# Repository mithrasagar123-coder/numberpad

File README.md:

# Numberpad

## Overview 

Behold! It is a numerical keypad that one may utilize to transcribe numerals. This splendiferous device will ensure that you can type as many numbers as your heart desires.

I designed this for my Week 5 project of halflife, a 10-week program where you can design and build hardware projects free of cost!

## Parts
* XIAO-nRF52840-SMD as the main microcontroller
* Four test points 
* 14 standard buttons and 3 big buttons to tap tap tap
* Diodes to prevent ghosting

## Schematic

## Board

## BOM
| Item | Qty | Supplier | Cost/item | Total Cost | Link |
|:---|:---|:---|:---|:---|:---|
| Seeed Studio XIAO nRF52840 | 1 | Seeed Studio | $4.99 | $4.99 | https://www.seeedstudio.com/Seeed-XIAO-BLE-nRF52840-p-5201.html?srsltid=AYCX9vLsY7zQQ4J1BxVNNOp9EBk7qKUEgk98Upe8GNEmZq4AKlAtIVR- |
| Keyboard hotswaps | 1 | Seeed Studio | $4.99 | $4.99 | ht
| Keyboard diodes 100pc | 1 | Amazon | $5.99 | $5.99 | https://www.amazon.com/Values-Switching-Recovery-Schottky-Rectifier/dp/B0D69Q6HXG/ref=sr_1_5?crid=ZRDEF7B4UF2C&dib=eyJ2IjoiMSJ9.zTXQrWobcfrHy7zOETXIjDRbmhPvQHa7WzTS4K5c7TtKBZmLvVPBBDGVQXcNNWnK3vHg6yybH8pVVuPdHUkF9WpLBnhPQ-BHFcxt8NnhxZ0JTi1DlANXWLTHb9LwpntcUGzXqZSMfTip11WtaIwqxSshLRQHVyd31PiwUklmBeasQo6x6BTMSYSnXaHhRht2aURJwXJJocz58Id0048wDufCg6wU0xVlsLu6lf77jNc.h6aZ6KuAbeSEJpQf2htEpvuIdWCliIb4IAxqaitKhro&dib_tag=se&keywords=1N5819%2Bdiodes&qid=1794433047&sprefix=1n5819%2Bdiode%2Caps%2C191&sr=8-5&th=1 |
| PCB | 1 | JLCPCB | $4.90 | $4.90 | https://cart.jlcpcb.com/quote?stencilLayer=2&stencilWidth=100&stencilLength=100&stencilCounts=5&plateType=1&spm=Jlcpcb.Homepage.1010&spm=Jlcpcb.Instantquote&_t=1794432060372&up_spm=Jlcpcb.Loginpage.1003 |
| Estimated total shipping |  |  |  | $8.23 |  |
| **Total** |  |  |  | **$** |  |

Thanks for reading!

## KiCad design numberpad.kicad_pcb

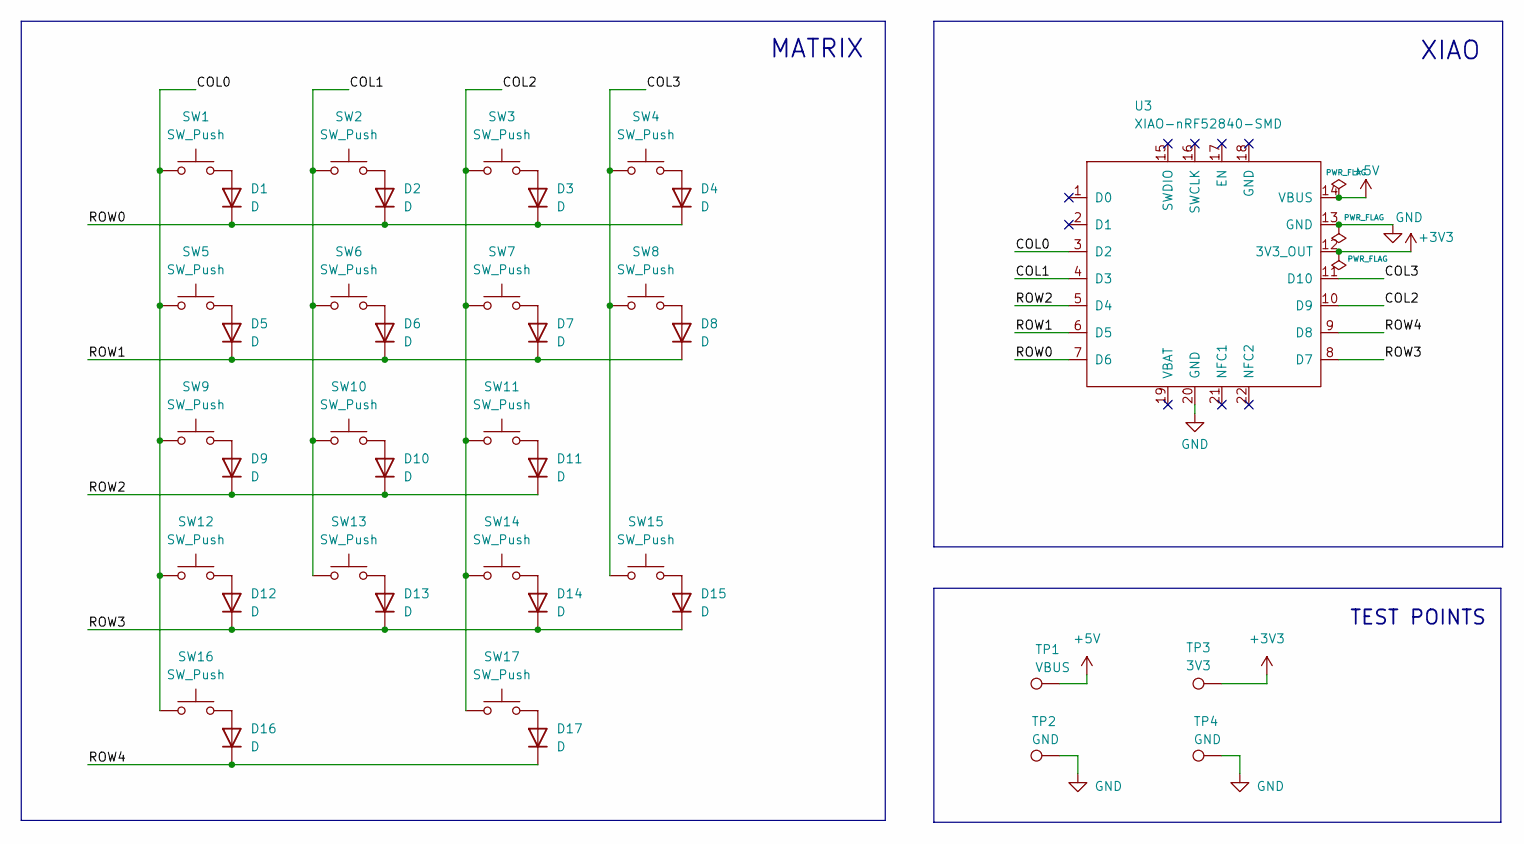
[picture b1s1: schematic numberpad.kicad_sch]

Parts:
D1, D2, D3, D4, D5, D6, D7, D8, D9, D10, D11, D12, D13, D14, D15, D16, D17: D; D_SOD-123
SW1, SW2, SW3, SW4, SW5, SW6, SW7, SW8, SW9, SW10, SW11, SW12, SW13, SW14, SW15, SW16, SW17: SW_Push; SW_choc_v2_HS_CPG135001S30_1u
TP1: VBUS; TestPoint_Pad_D2.0mm
TP2, TP4: GND; TestPoint_Pad_D2.0mm
TP3: 3V3; TestPoint_Pad_D2.0mm
U3: XIAO-nRF52840-SMD; modified-XIAO-nRF52840-SMD

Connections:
+3V3: TP3.1 (1_1), U3.12 (3V3_OUT)
+5V: TP1.1 (1_1), U3.14 (VBUS)
/COL0: SW1.1, SW5.1, SW9.1, SW12.1, SW16.1, U3.3 (D2)
/COL1: SW2.1, SW6.1, SW10.1, SW13.1, U3.4 (D3)
/COL2: SW3.1, SW7.1, SW11.1, SW14.1, SW17.1, U3.10 (D9)
/COL3: SW4.1, SW8.1, SW15.1, U3.11 (D10)
/ROW0: D1.1 (K), D2.1 (K), D3.1 (K), D4.1 (K), U3.7 (D6)
/ROW1: D5.1 (K), D6.1 (K), D7.1 (K), D8.1 (K), U3.6 (D5)
/ROW2: D9.1 (K), D10.1 (K), D11.1 (K), U3.5 (D4)
/ROW3: D12.1 (K), D13.1 (K), D14.1 (K), D15.1 (K), U3.8 (D7)
/ROW4: D16.1 (K), D17.1 (K), U3.9 (D8)
GND: TP2.1 (1_1), TP4.1 (1_1), U3.13 (GND), U3.20 (GND)
unnamed: D1.2 (A), SW1.2
unnamed: D2.2 (A), SW2.2
unnamed: D3.2 (A), SW3.2
unnamed: D4.2 (A), SW4.2
unnamed: D5.2 (A), SW5.2
unnamed: D6.2 (A), SW6.2
unnamed: D7.2 (A), SW7.2
unnamed: D8.2 (A), SW8.2
unnamed: D9.2 (A), SW9.2
unnamed: D10.2 (A), SW10.2
unnamed: D11.2 (A), SW11.2
unnamed: D12.2 (A), SW12.2
unnamed: D13.2 (A), SW13.2
unnamed: D14.2 (A), SW14.2
unnamed: D15.2 (A), SW15.2
unnamed: D16.2 (A), SW16.2
unnamed: D17.2 (A), SW17.2

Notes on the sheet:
TEST POINTS
MATRIX
XIAO

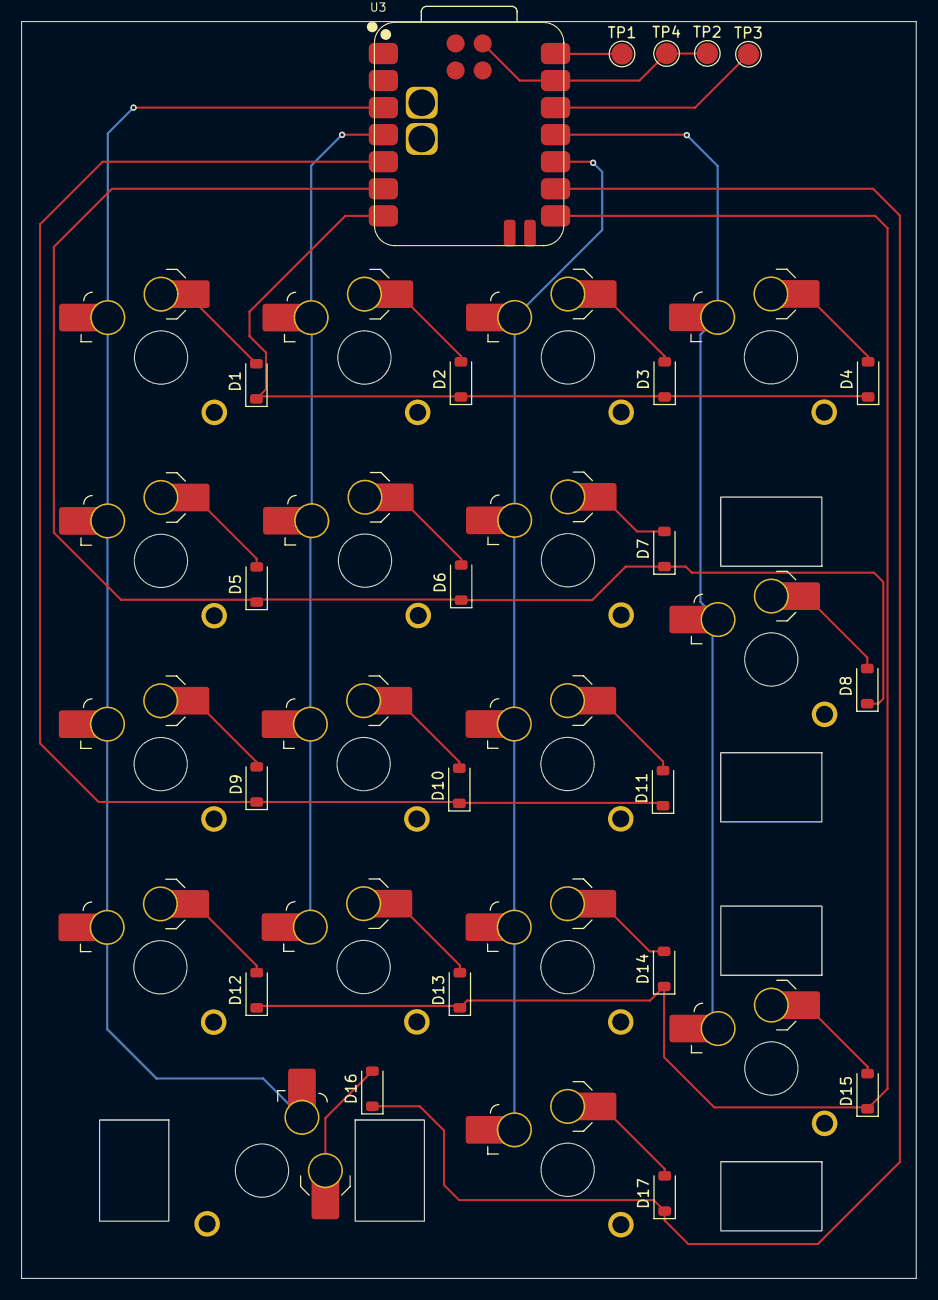
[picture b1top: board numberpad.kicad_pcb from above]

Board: 2 copper layers, 84.0 x 118.0 mm, 39 parts (0 on the bottom side), 29 nets.
